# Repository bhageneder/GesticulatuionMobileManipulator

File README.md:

# Gesticulation Mobile Manipulator
Embedded Engineering Project Summer 2024

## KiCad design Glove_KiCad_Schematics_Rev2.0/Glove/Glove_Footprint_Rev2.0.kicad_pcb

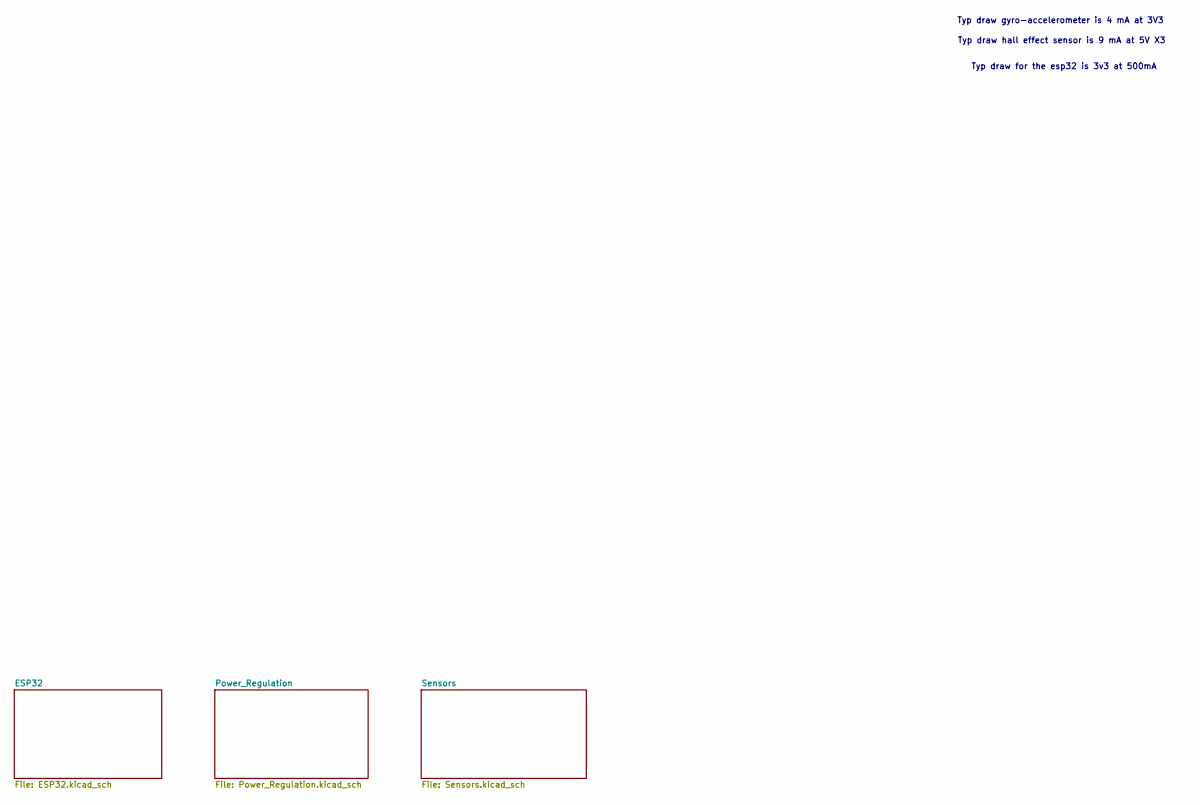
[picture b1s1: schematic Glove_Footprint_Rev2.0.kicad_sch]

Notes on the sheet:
Typ draw for the esp32 is 3v3 at 500mA
Typ draw hall effect sensor is 9 mA at 5V X3
Typ draw gyro-accelerometer is 4 mA at 3V3

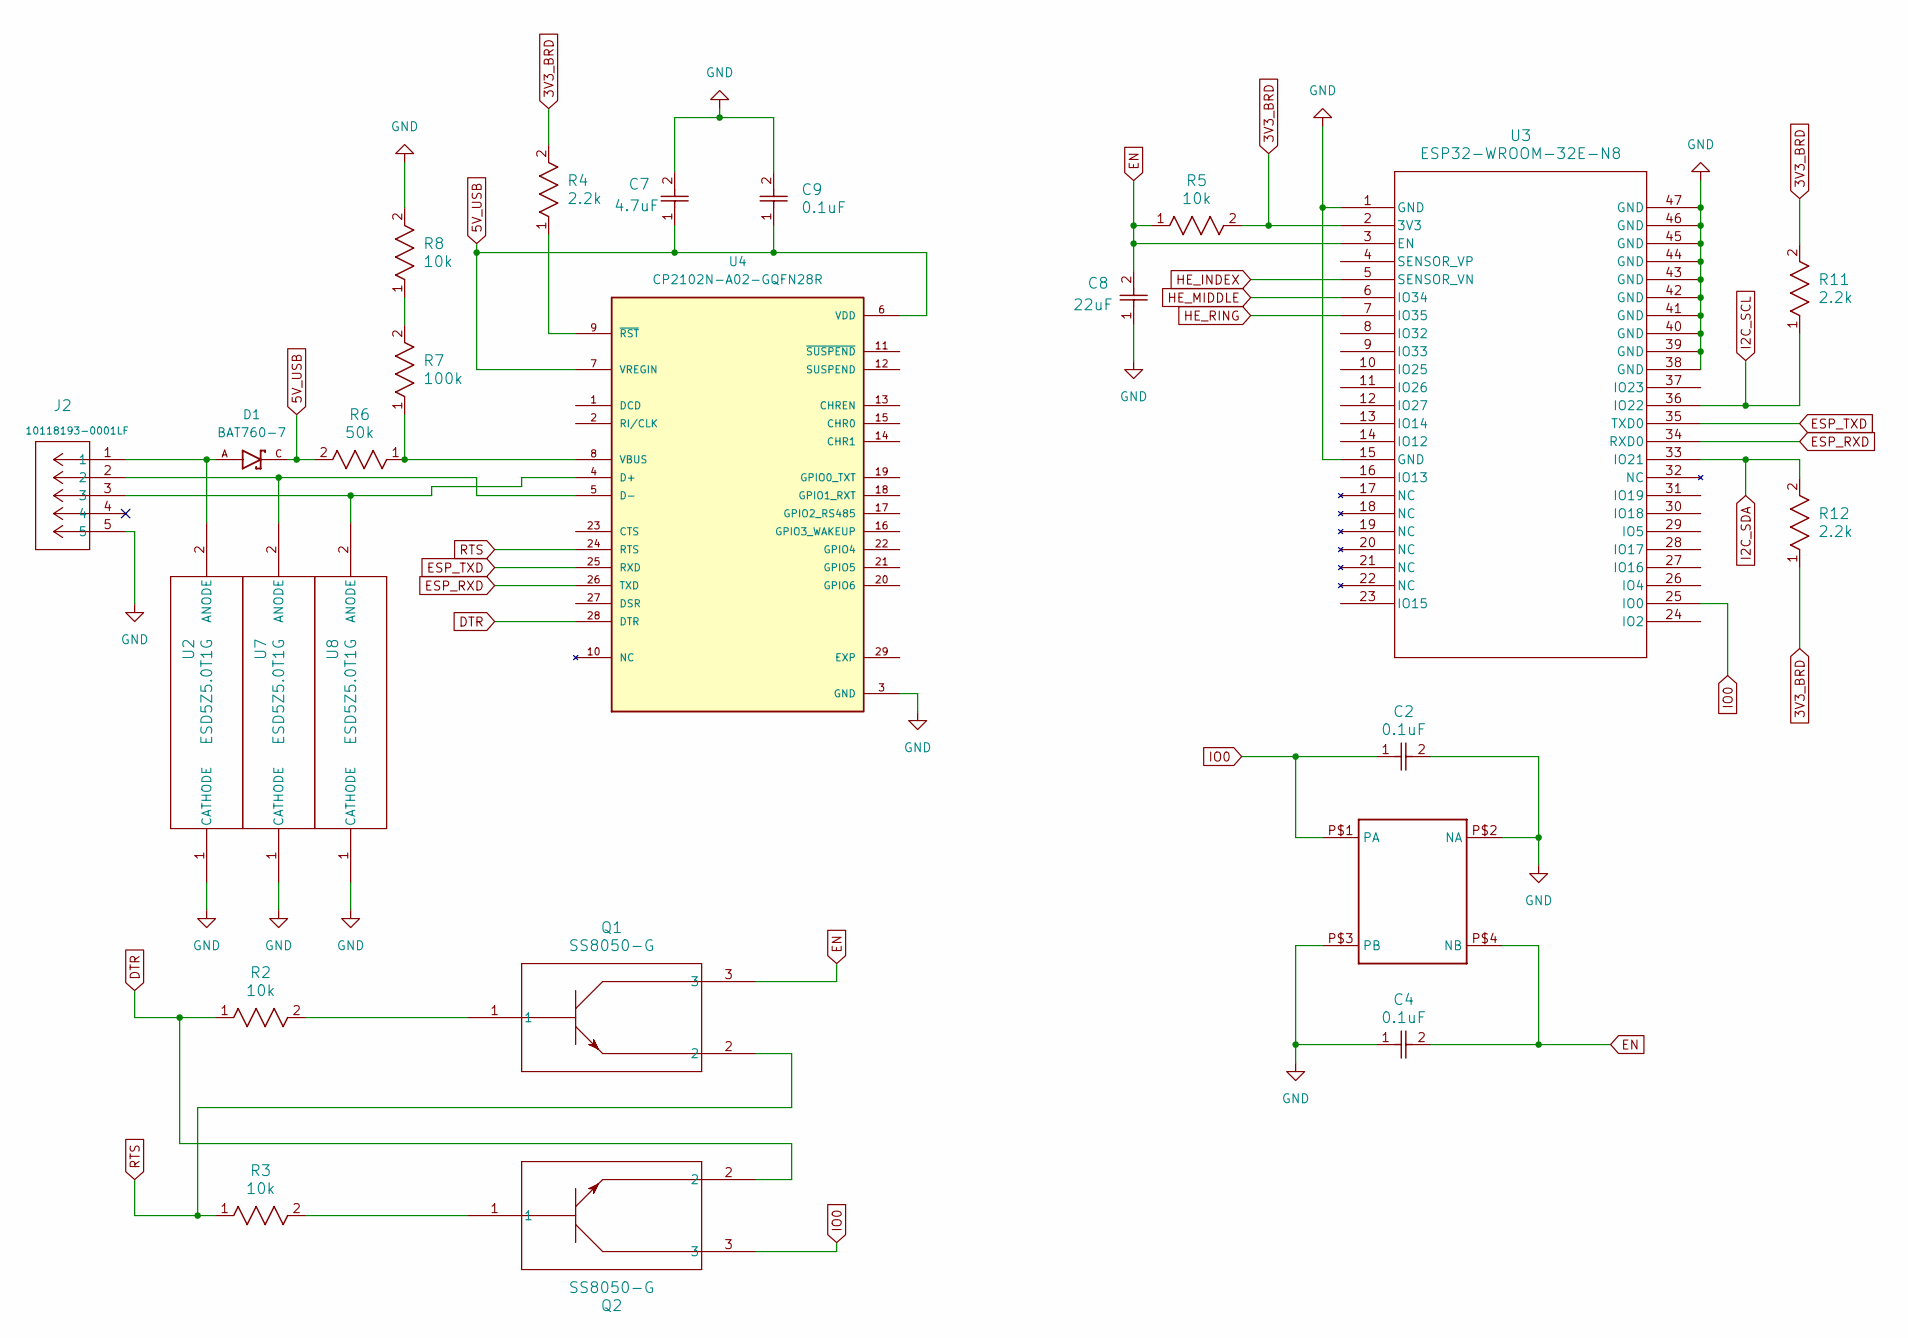
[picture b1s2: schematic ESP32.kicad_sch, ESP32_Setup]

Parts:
C2, C4, C9: 0.1uF; G-155_MUR-L
C7: 4.7uF; CAP_GRM188R61A106ME69D_MUR
C8: 22uF; CAP_GRM188R61A106ME69D_MUR
D1: BAT760-7; SOD2513X120N; PARTREV 9-2
J2: 10118193-0001LF; CONN_10118193-0001LF_AMP
Q1, Q2: SS8050-G; TRAN_SS8050-G_CIP-L
R2, R3, R5, R8: 10k; RC0402N_YAG
R4, R11, R12: 2.2k; RC0402N_YAG
R6: 50k; RC0402N_YAG
R7: 100k; RC0402N_YAG
S1: 219-2LPST
U2, U7, U8: ESD5Z5.0T1G; SOD-523_0P9X1P3_ONS-L
U3: ESP32-WROOM-32E-N8; ESP32­WROOM­32E_EXP
U4: CP2102N-A02-GQFN28R; IC_CP2102N-A02-GQFN28R; PARTREV 1.5

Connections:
3V3_BRD: R4.2, R5.2, R11.2, R12.1, U3.2 (3V3); also elsewhere on the board
5V_USB: C7.1, C9.1, D1.C, R6.2, U4.6 (VDD), U4.7 (VREGIN); also elsewhere on the board
DTR: Q2.2, R2.1, U4.28 (DTR)
EN: C4.2, C8.2, Q1.3, R5.1, S1.P$4 (NB), U3.3 (EN)
ESP_RXD: U3.34 (RXD0), U4.26 (TXD)
ESP_TXD: U3.35 (TXD0), U4.25 (RXD)
GND: C2.2, C4.1, C7.2, C8.1, C9.2, J2.5, R8.2, S1.P$2 (NA), S1.P$3 (PB), U2.1 (CATHODE), U3.1 (GND), U3.15 (GND), U3.38 (GND), U3.39 (GND), U3.40 (GND), U3.41 (GND), U3.42 (GND), U3.43 (GND), U3.44 (GND), U3.45 (GND), U3.46 (GND), U3.47 (GND), U4.3 (GND), U7.1 (CATHODE), U8.1 (CATHODE); also elsewhere on the board
HE_INDEX: U3.5 (SENSOR_VN); also elsewhere on the board
HE_MIDDLE: U3.6 (IO34); also elsewhere on the board
HE_RING: U3.7 (IO35); also elsewhere on the board
I2C_SCL: R11.1, U3.36 (IO22); also elsewhere on the board
I2C_SDA: R12.2, U3.33 (IO21); also elsewhere on the board
IO0: C2.1, Q2.3, S1.P$1 (PA), U3.25 (IO0)
unnamed: Q1.1, R2.2
unnamed: Q2.1, R3.2
unnamed: R7.2, R8.1
unnamed: D1.A, J2.1, U2.2 (ANODE)
unnamed: J2.3, U4.4 (D+), U8.2 (ANODE)
unnamed: J2.2, U4.5 (D-), U7.2 (ANODE)
unnamed: R6.1, R7.1, U4.8 (VBUS)
unnamed: R4.1, U4.9 (~RST)
RTS: Q1.2, R3.1, U4.24 (RTS)

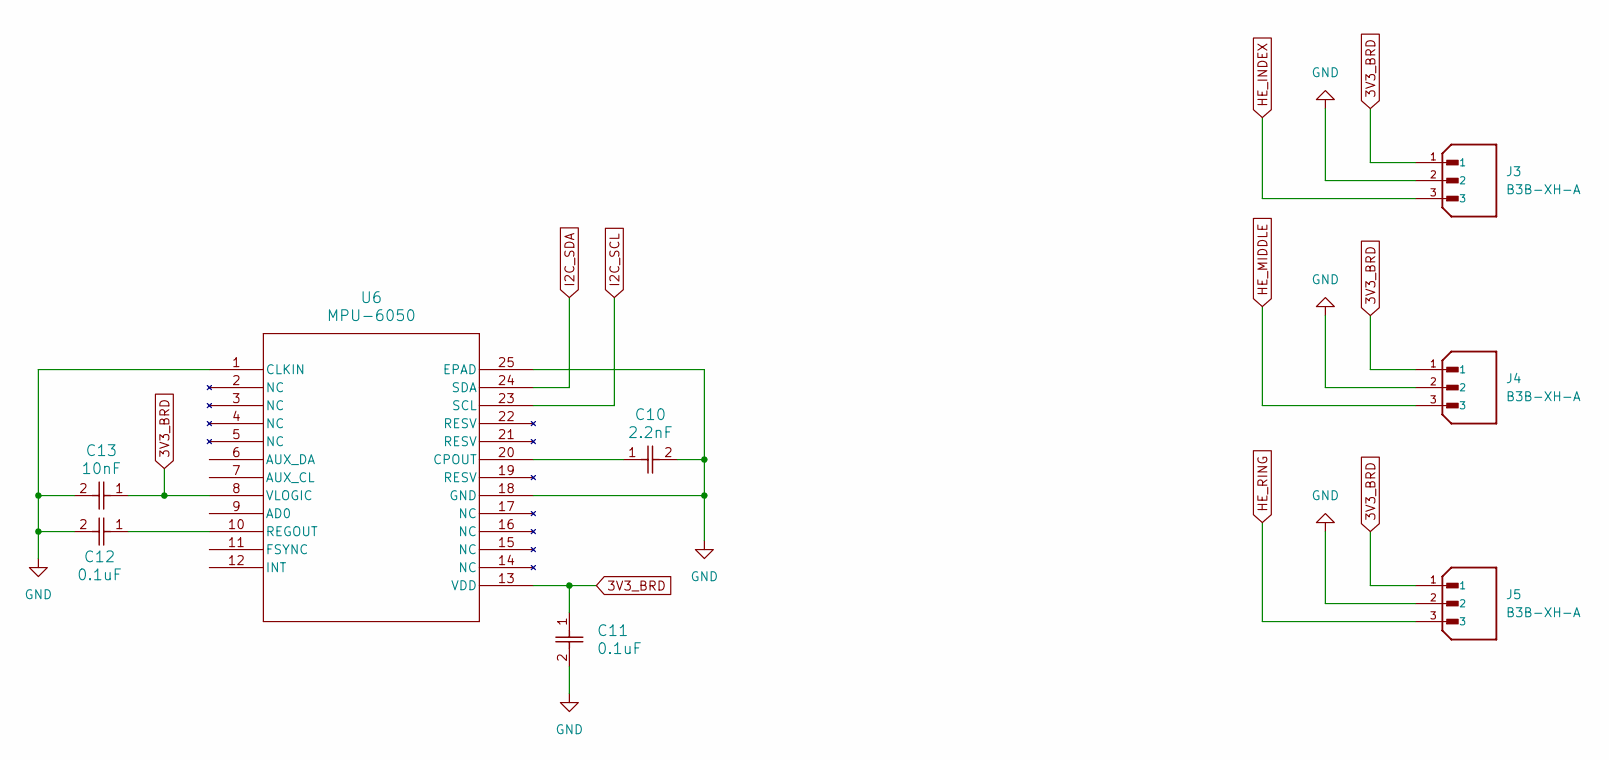
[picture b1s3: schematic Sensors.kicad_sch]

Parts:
C10: 2.2nF; G-155_MUR-L
C11, C12: 0.1uF; G-155_MUR-L
C13: 10nF; G-155_MUR-L
J3, J4, J5: B3B-XH-A; JST_B3B-XH-A; PARTREV 7/4/21
U6: MPU-6050; QFN24_4X4X0P9-0P5_TDK-L

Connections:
3V3_BRD: C11.1, C13.1, J3.1, J4.1, J5.1, U6.8 (VLOGIC), U6.13 (VDD); also elsewhere on the board
GND: C10.2, C11.2, C12.2, C13.2, J3.2, J4.2, J5.2, U6.1 (CLKIN), U6.18 (GND), U6.25 (EPAD); also elsewhere on the board
HE_INDEX: J3.3; also elsewhere on the board
HE_MIDDLE: J4.3; also elsewhere on the board
HE_RING: J5.3; also elsewhere on the board
I2C_SCL: U6.23 (SCL); also elsewhere on the board
I2C_SDA: U6.24 (SDA); also elsewhere on the board
unnamed: C10.1, U6.20 (CPOUT)
unnamed: C12.1, U6.10 (REGOUT)

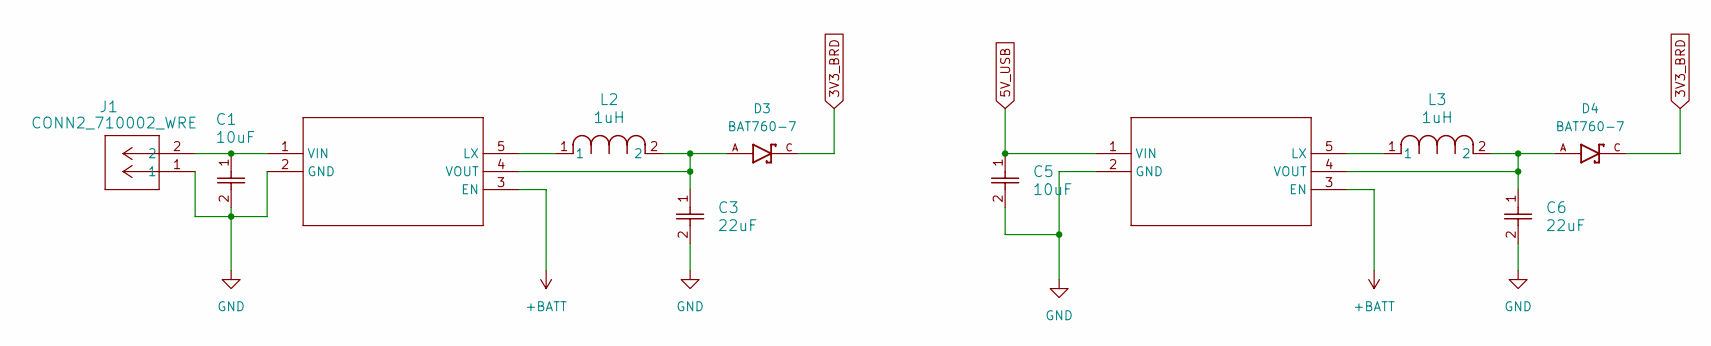
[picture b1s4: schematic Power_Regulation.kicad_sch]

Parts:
C1, C5: 10uF; CAP_GRM188R61A106ME69D_MUR
C3, C6: 22uF; CAP_GRM188R61A106ME69D_MUR
D3, D4: BAT760-7; SOD2513X120N; PARTREV 9-2
J1: CONN2_710002_WRE
L2, L3: 1uH; DFE252012P-1R0M=P2
U1, U5: SOT23-5-SC189_SEM

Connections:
3V3_BRD: D3.C, D4.C; also elsewhere on the board
5V_USB: C5.1, U5.1 (VIN); also elsewhere on the board
+BATT: U1.3 (EN), U5.3 (EN)
GND: C1.2, C3.2, C5.2, C6.2, J1.1, U1.2 (GND), U5.2 (GND); also elsewhere on the board
unnamed: L2.1, U1.5 (LX)
unnamed: C1.1, J1.2, U1.1 (VIN)
unnamed: C3.1, D3.A, L2.2, U1.4 (VOUT)
unnamed: L3.1, U5.5 (LX)
unnamed: C6.1, D4.A, L3.2, U5.4 (VOUT)

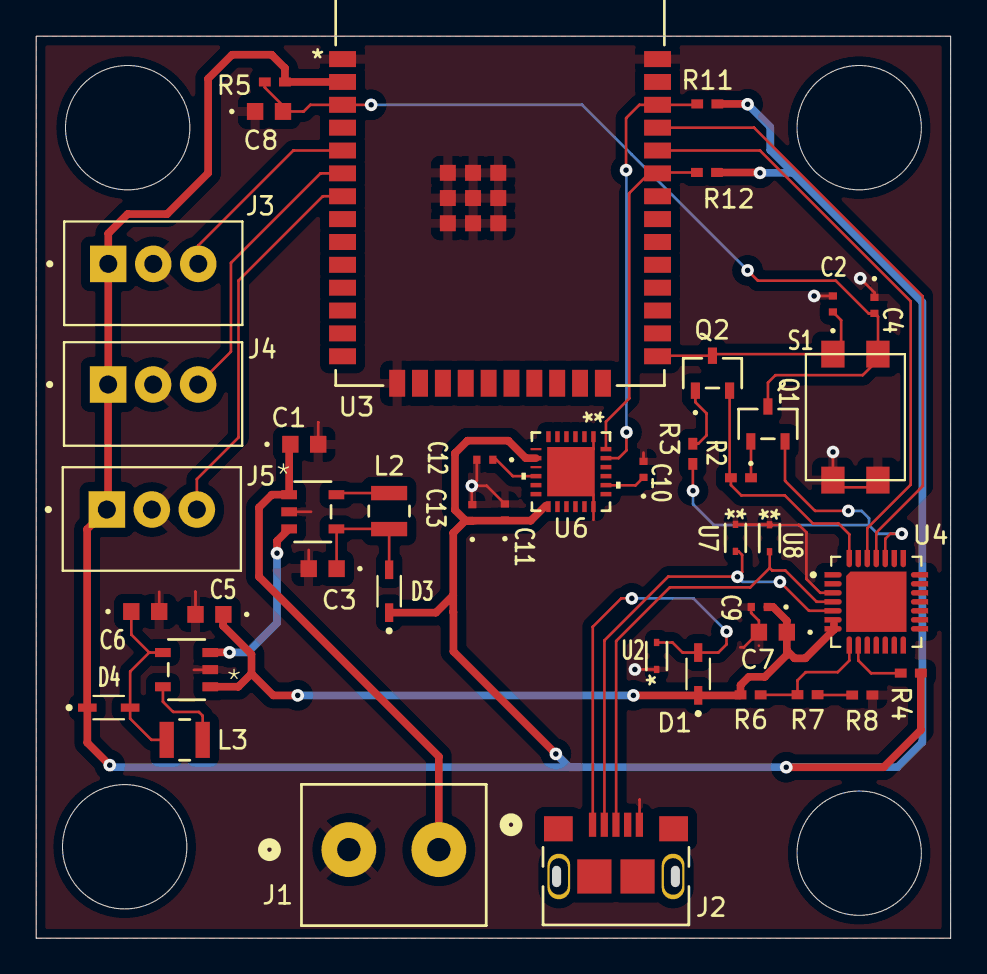
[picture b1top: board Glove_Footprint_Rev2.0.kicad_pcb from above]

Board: 2 copper layers, 50.3 x 49.6 mm, 43 parts (0 on the bottom side), 30 nets.

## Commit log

2024-07-01 Uploading PCB Schematics Rev2.0
2024-07-07 Added basic web server and servo controller
2024-07-07 Adding Cart / Arm KiCad Schematics
2024-07-17 Add files via upload
    Glove_ESP.ino - Reads positional values from a gyro-accelerometer and sends them over ESP_NOW. MAC address is currently configured to the esp in my (Brandon) system, so will need to be updated depend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
    main.cpp - Microros implementation that will receive arguments from Glove_ESP.ino, perform some logic, then publish to the moveit planner. Currently the values that are being published are set to inc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
    moveit_handler - Node
2024-07-22 Full functionality (unpolished) from glove to cart+arm
    Glove_ESP - Connected to gyro-accelerometer. Outputs a direction to the main.cpp (microros file) over ESP_NOW.
    main.cpp - Receives direction from ESP_NOW, updates position based off of the direction, publishes position to moveit_handler, subscribes to joint states from
    moveit_handler, sends joint states to cart_and_arm over ESP_NOW.
    cart_and-arm: Currently just prints joint states received from ESP_NOW
2024-07-22 Cart Code Update
2024-07-29 Refactored file system and updated cart/arm/servotest scripts
2024-08-05 Tested Oscillator Frequency for PWM signals
2024-08-06 Update main.ino
    Included code for cart movement from accel positions.
2024-08-06 Partially Complete
    - Partial functionality in arm movement commands
    - Full functionality in cart movement commands
    - Full functionality in finger 'touching'
2024-08-06 Update cart and test files
